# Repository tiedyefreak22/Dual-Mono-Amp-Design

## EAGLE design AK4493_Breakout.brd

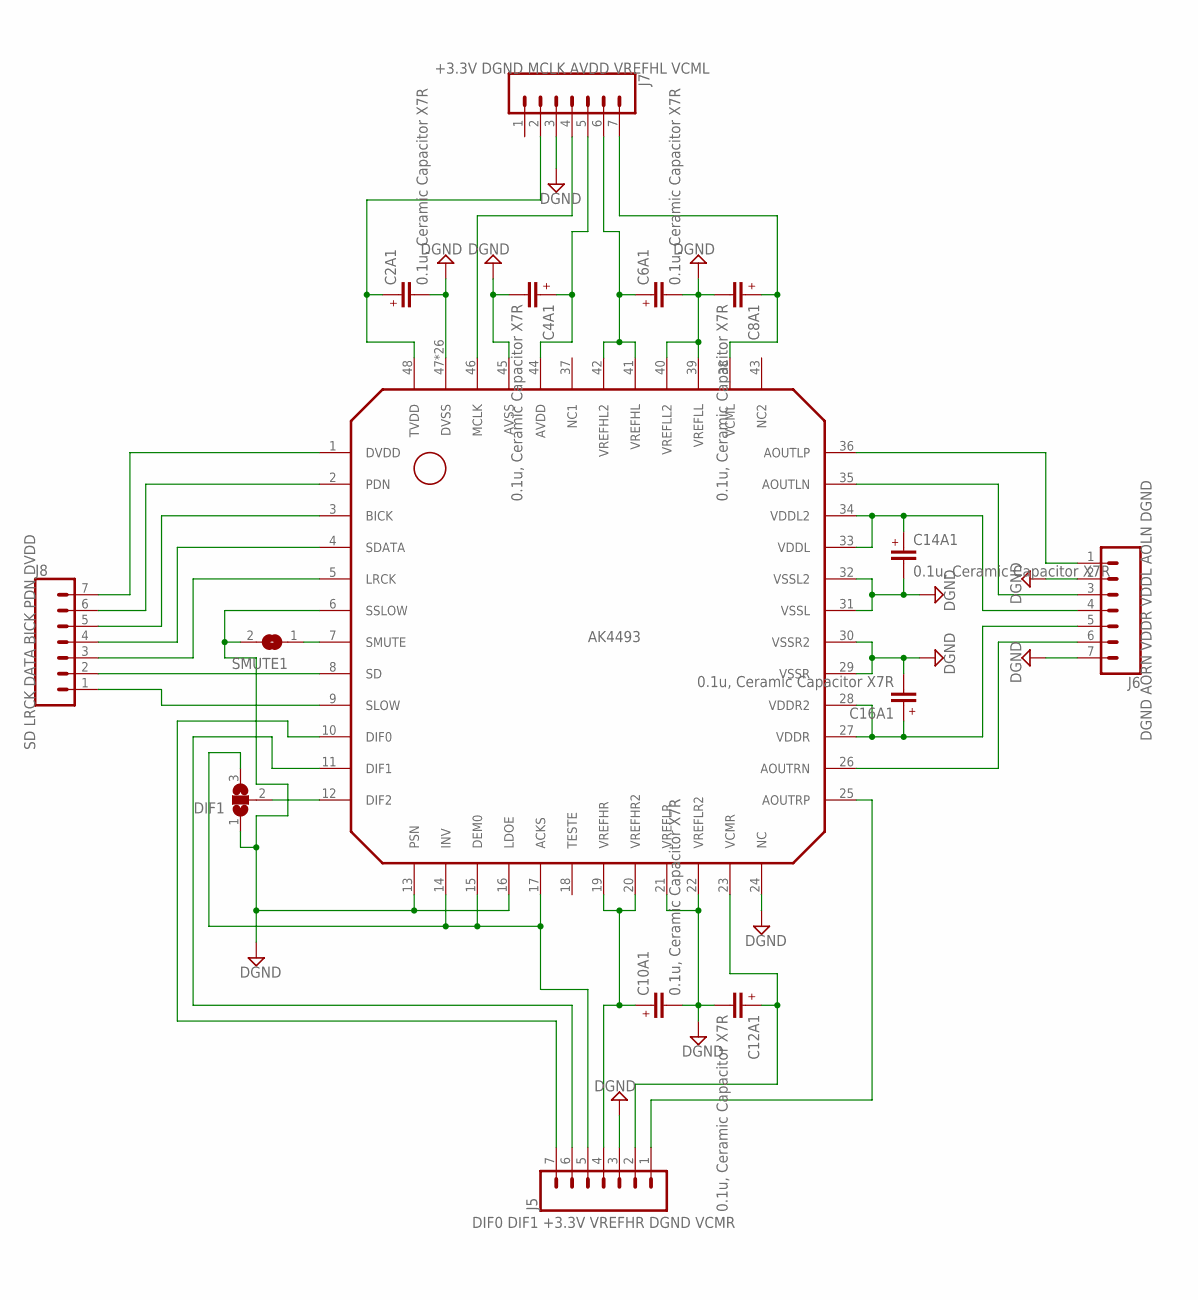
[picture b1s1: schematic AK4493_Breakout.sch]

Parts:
C2A1, C4A1, C6A1, C8A1, C10A1, C12A1, C14A1, C16A1: 0.1u, Ceramic Capacitor X7R; C0603K
DIF1: SJ2W; SJ_2
IC2: AK4493; LQFP48_
J5, J6, J7, J8: CONN_07; 1X07
SMUTE1: SJ

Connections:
DGND: C2A1.2, C2A1.DGND (2), C4A1.2, C4A1.DGND (2), C6A1.2, C6A1.DGND (2), C8A1.2, C8A1.DGND (2), C10A1.2, C10A1.DGND (2), C12A1.2, C12A1.DGND (2), C14A1.2, C14A1.DGND (2), C16A1.2, C16A1.DGND (2), DIF1.1, IC2.6 (SSLOW), IC2.13 (PSN), IC2.16 (LDOE), IC2.21 (VREFLR), IC2.22 (VREFLR2), IC2.24 (NC), IC2.29 (VSSR), IC2.30 (VSSR2), IC2.31 (VSSL), IC2.32 (VSSL2), IC2.39 (VREFLL), IC2.40 (VREFLL2), IC2.45 (AVSS), IC2.47 (DVSS), IC2.P$1 (DVSS), IC2.P$2 (DVSS), IC2.P$3 (DVSS), IC2.P$4 (DVSS), IC2.P$5 (DVSS), IC2.P$6 (DVSS), IC2.P$7 (DVSS), IC2.P$8 (DVSS), IC2.P$9 (DVSS), IC2.P$10 (DVSS), IC2.P$11 (DVSS), IC2.P$12 (DVSS), IC2.P$13 (DVSS), IC2.P$14 (DVSS), IC2.P$15 (DVSS), IC2.P$16 (DVSS), IC2.P$17 (DVSS), IC2.P$18 (DVSS), IC2.P$19 (DVSS), IC2.P$20 (DVSS), IC2.P$21 (DVSS), IC2.P$22 (DVSS), IC2.P$23 (DVSS), IC2.P$24 (DVSS), IC2.P$25 (DVSS), J5.3, J6.2, J6.7, J7.3, SMUTE1.2
unnamed: IC2.36 (AOUTLP), J6.1
unnamed: IC2.35 (AOUTLN), J6.3
unnamed: IC2.25 (AOUTRP), J5.1
unnamed: IC2.26 (AOUTRN), J6.6
unnamed: IC2.9 (SLOW), J8.1
unnamed: IC2.10 (DIF0), J5.7
unnamed: IC2.5 (LRCK), J8.3
unnamed: IC2.4 (SDATA), J8.4
unnamed: IC2.3 (BICK), J8.5
unnamed: IC2.46 (MCLK), J7.4
unnamed: IC2.1 (DVDD), J8.7
unnamed: C4A1.1, IC2.44 (AVDD), J7.5
unnamed: IC2.2 (PDN), J8.6
unnamed: C8A1.1, IC2.38 (VCML), J7.7
unnamed: C12A1.1, IC2.23 (VCMR), J5.2
unnamed: C6A1.1, IC2.41 (VREFHL), IC2.42 (VREFHL2), J7.6
unnamed: DIF1.2, IC2.12 (DIF2)
unnamed: IC2.7 (SMUTE), SMUTE1.1
unnamed: IC2.8 (SD), J8.2
unnamed: IC2.11 (DIF1), J5.6
unnamed: C10A1.1, IC2.19 (VREFHR), IC2.20 (VREFHR2), J5.4
unnamed: C14A1.1, IC2.33 (VDDL), IC2.34 (VDDL2), J6.4
unnamed: C16A1.1, IC2.27 (VDDR), IC2.28 (VDDR2), J6.5
unnamed: C2A1.1, IC2.48 (TVDD), J7.2
unnamed: DIF1.3, IC2.14 (INV), IC2.15 (DEM0), IC2.17 (ACKS), J5.5

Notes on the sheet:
+3.3V DGND MCLK AVDD VREFHL VCML
DIF0 DIF1 +3.3V VREFHR DGND VCMR
SD LRCK DATA BICK PDN DVDD
DGND AORN VDDR VDDL AOLN DGND

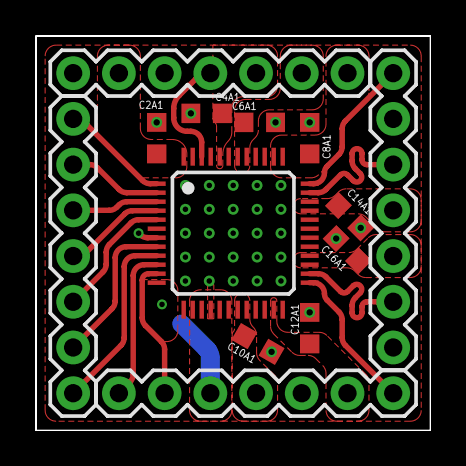
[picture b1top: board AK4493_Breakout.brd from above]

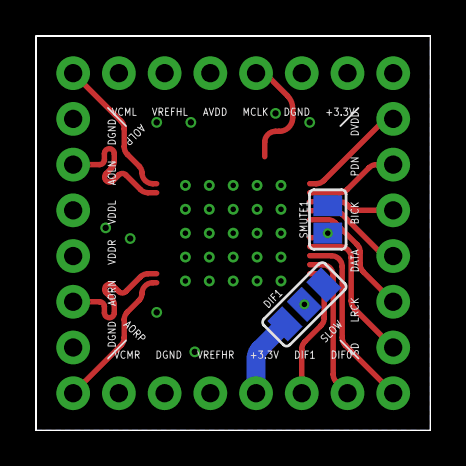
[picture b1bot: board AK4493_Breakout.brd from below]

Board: 2 copper layers, 21.9 x 21.9 mm, 15 parts (2 on the bottom side), 26 nets.

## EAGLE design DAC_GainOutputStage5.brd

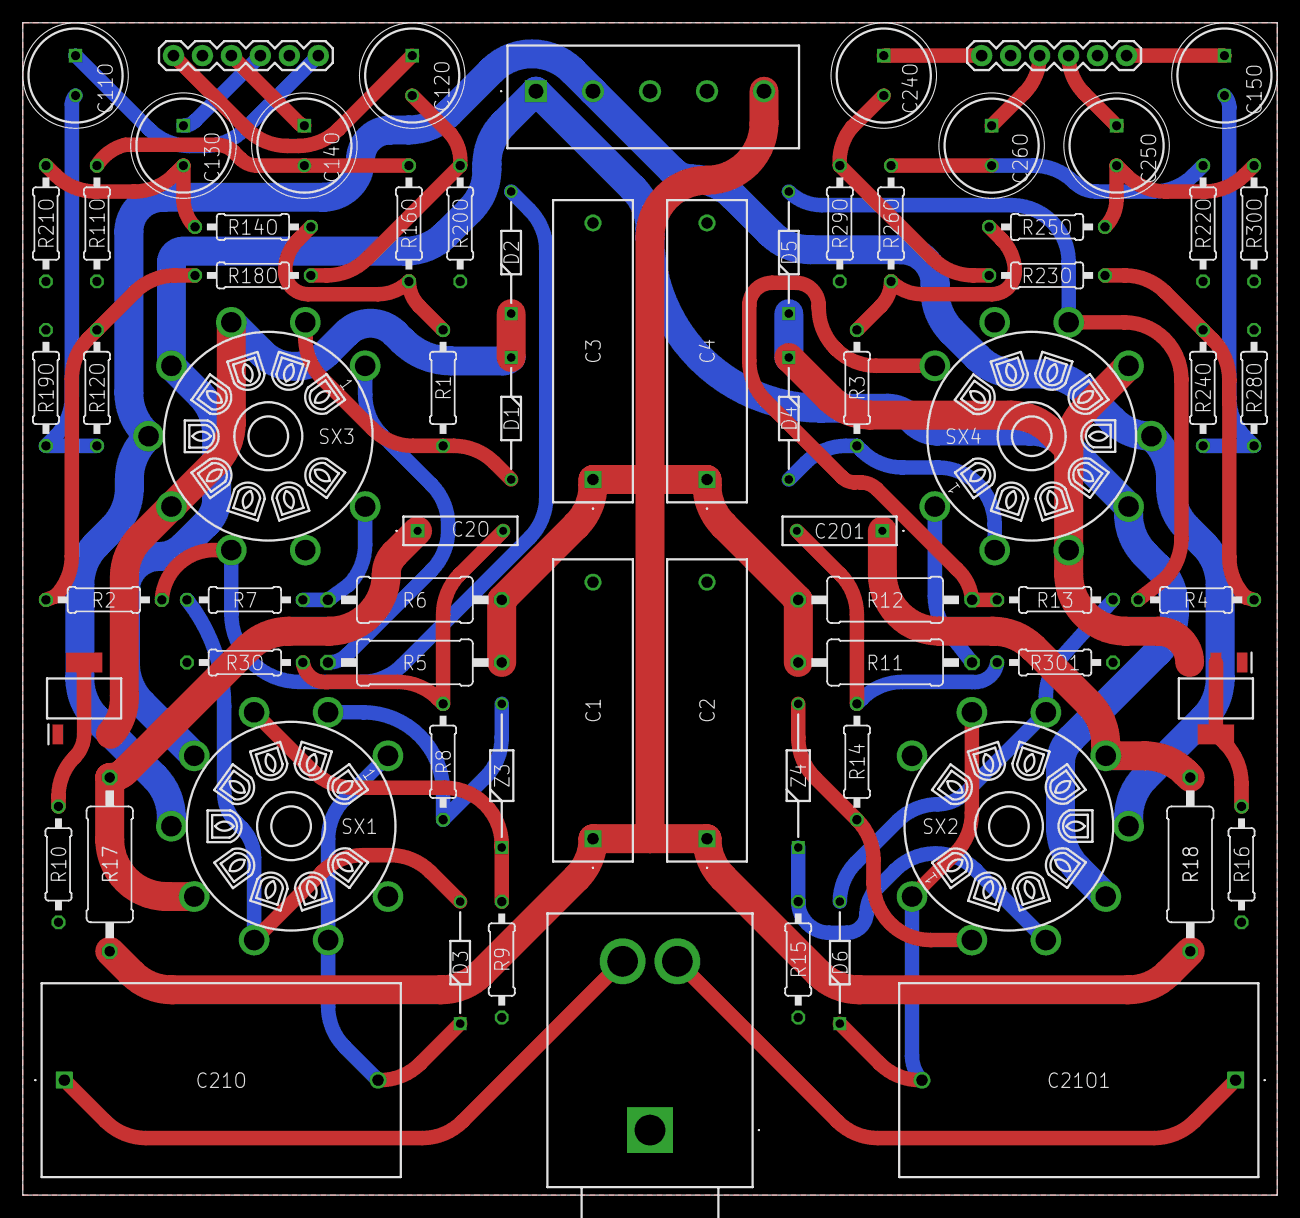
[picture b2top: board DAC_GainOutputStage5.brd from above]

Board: 2 copper layers, 110.0 x 102.8 mm, 70 parts (0 on the bottom side), 50 nets.

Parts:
C1, C2, C3, C4: MKP4G034705D00KSSD
C2O, C2O1: 0.1uF, 35V; MKS4B031002A00JC00
C11O, C12O, C13O, C14O, C15O, C24O, C25O, C26O: 100uF; CAPPRD350W60D825H1300
C21O, C21O1: 30uF/400V; DCP4G053006ID2KSSD
D1, D2, D3, D4, D5, D6: 1N4148-T50R; DIOAD1068W53L380D172
J1: 1935190
J2, J13: 1X06
J3: SJ-63033A; SJ63033A
R1, R2, R3, R4, R7, R8, R13, R14: 1k; 0207/10
R3O, R3O1: 1M*; 0207/10
R5, R6, R11, R12: 9.1k; 0411/15
R9, R15: 330; 0207/10
R10, R16: 48.7; 0207/10
R11O, R19O, R20O, R21O, R22O, R28O, R29O, R30O: 10k; 0207/10
R12O, R14O, R16O, R18O, R23O, R24O, R25O, R26O: 182; 0207/10
R17, R18: 499; 0411/15
SX1, SX2, SX3, SX4: VT9-PT
U1, U2: LM317MQDCYR; SOT230P700X180-4N
Z3, Z4: 1N750; DIOAD1256W56L444D203

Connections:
66.3VAC/1: J1.1, SX1.4, SX2.4, SX3.4, SX4.4
66.3VAC/2: J1.2, SX1.5, SX2.5, SX3.5, SX4.5
+240VDC: C1.1, C2.1, C3.1, C4.1, J1.5, R5.2, R6.2, R11.2, R12.2, R17.1, R18.2
AGND: C1.2, C2.2, C3.2, C4.2, J1.4, J2.2, J2.5, J3.1, J13.2, J13.5, R3O.2, R3O1.2, R9.1, R10.1, R11O.2, R15.1, R16.1, R19O.1, R20O.2, R21O.1, R22O.2, R28O.1, R29O.2, R30O.1, U1.1, U2.1
L+: R4.2, R23O.1, R24O.1
L-: R3.2, R25O.1, R26O.1
L_OUT: C21O1.1, J3.2
unnamed: R6.1, R7.2, SX3.9
unnamed: R8.1, SX1.2, Z3.2
unnamed: C21O1.2, D6.1, SX2.1, SX2.8
unnamed: D4.2, R3.1, SX4.2
unnamed: D5.2, R4.1, SX4.7
unnamed: D1.2, R1.1, SX3.2
unnamed: D4.1, D5.1, SX4.3, SX4.6, U2.3
unnamed: R11.1, SX4.1
unnamed: R12.1, R13.2, SX4.9
unnamed: C11O.1, J13.6
unnamed: C11O.2, R12O.2, R19O.2
unnamed: C15O.1, J2.6
unnamed: D2.2, R2.1, SX3.7
unnamed: R14.1, SX2.2, Z4.2
unnamed: C12O.1, J13.1
unnamed: C2O.2, R3O.1, R8.2
unnamed: C2O1.2, R3O1.1, R14.2
unnamed: C21O.2, D3.1, SX1.1, SX1.8
unnamed: C12O.2, R18O.2, R20O.1
unnamed: C15O.2, R24O.2, R28O.2
unnamed: C13O.1, J13.4
unnamed: D1.1, D2.1, SX3.3, SX3.6, U1.3
unnamed: D3.2, R7.1, SX1.7
unnamed: C14O.1, J13.3
unnamed: C14O.2, R11O.1, R16O.2
unnamed: R9.2, SX1.3, Z3.1
unnamed: R15.2, SX2.3, Z4.1
unnamed: C13O.2, R14O.2, R21O.2
unnamed: D6.2, R13.1, SX2.7
unnamed: C24O.1, J2.1
unnamed: C24O.2, R23O.2, R29O.1
unnamed: C25O.1, J2.4
unnamed: C26O.1, J2.3
unnamed: C26O.2, R22O.1, R26O.2
unnamed: R5.1, SX3.1
unnamed: C25O.2, R25O.2, R30O.2
unnamed: R10.2, U1.2, U1.4
unnamed: R16.2, U2.2, U2.4
unnamed: C2O.1, R17.2, SX1.6
unnamed: C2O1.1, R18.1, SX2.6
R+: R2.2, R12O.1, R18O.1
R-: R1.2, R14O.1, R16O.1
R_OUT: C21O.1, J3.3

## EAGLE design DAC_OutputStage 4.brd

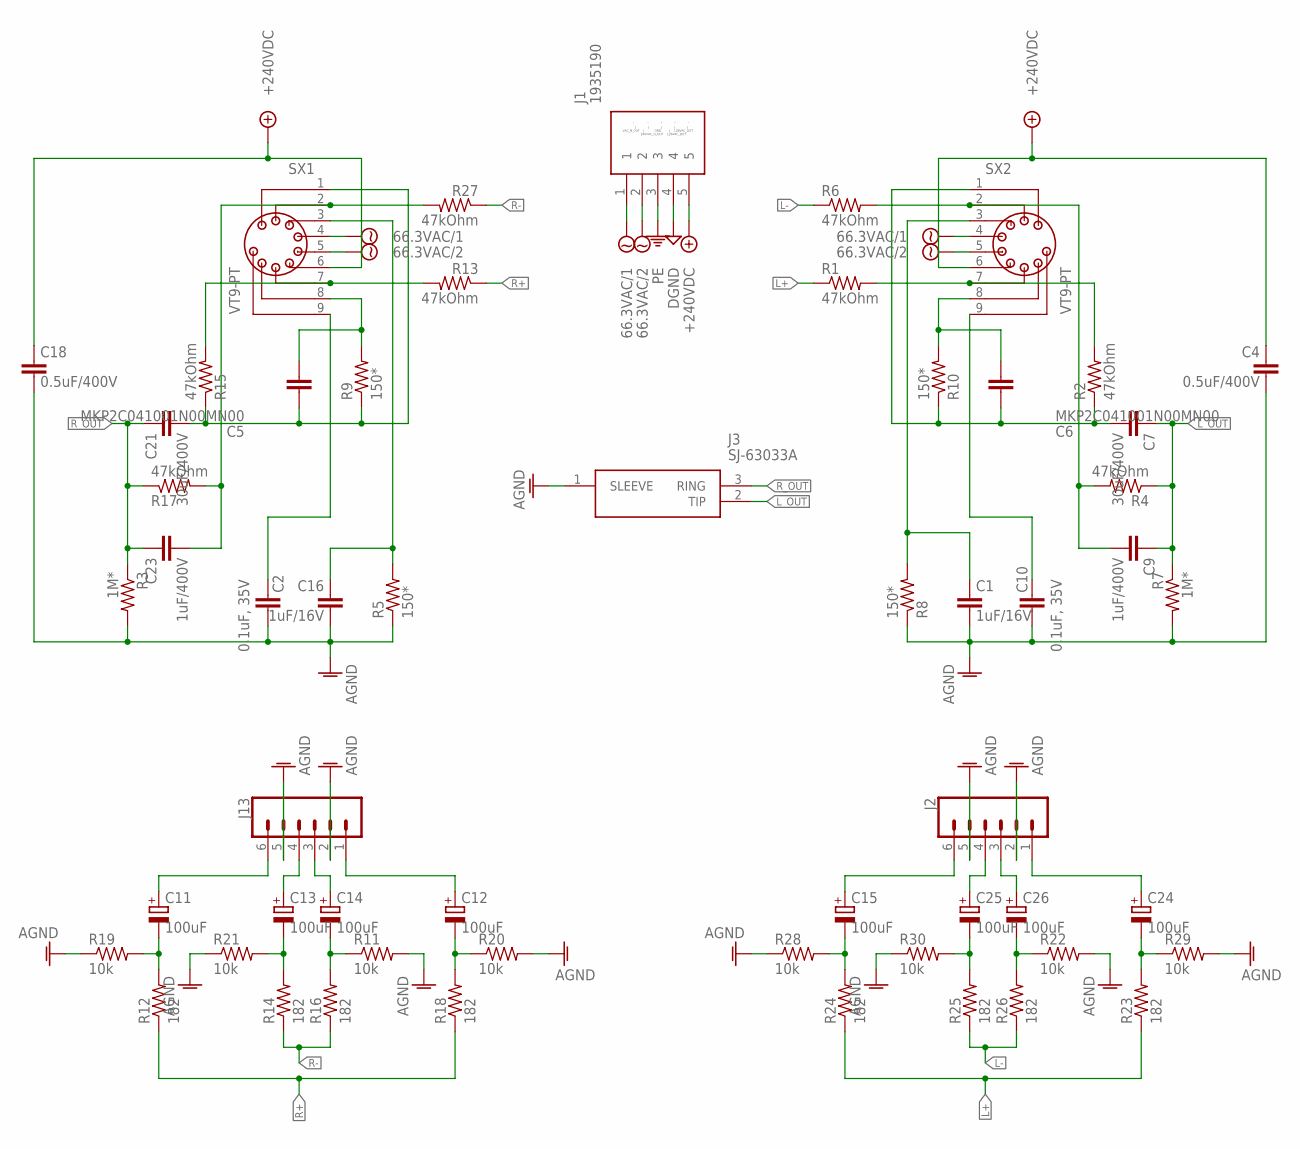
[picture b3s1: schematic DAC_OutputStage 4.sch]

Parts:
C1, C16: 1uF/16V; MKP2C041001N00MN00
C2, C10: 0.1uF, 35V; MKS4B031002A00JC00
C4, C18: 0.5uF/400V; MKP4G034705D00KSSD
C5, C6: MKP2C041001N00MN00
C7, C21: 30uF/400V; DCP4G053006ID2KSSD
C9, C23: 1uF/400V; MKP4G041005I00JSSD
C11, C12, C13, C14, C15, C24, C25, C26: 100uF; CAPPRD350W60D825H1300
J1: 1935190
J2, J13: CONN_06SILK_FEMALE_PTH; 1X06
J3: SJ-63033A; SJ63033A
R1, R2, R4, R6, R13, R15, R17, R27: 47kOhm; RESAD1540W55L620D230
R3, R7: 1M*; RESAD1540W60L620D230
R5, R8, R9, R10: 150*; RESAD1540W55L620D230
R11, R19, R20, R21, R22, R28, R29, R30: 10k; RESAD1540W55L620D230
R12, R14, R16, R18, R23, R24, R25, R26: 182; RESAD1590W60L630D240
SX1, SX2: VT9-PT

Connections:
66.3VAC/1: J1.1, SX1.4, SX2.4
66.3VAC/2: J1.2, SX1.5, SX2.5
+240VDC: C4.1, C18.1, J1.5, SX1.6, SX2.6
AGND: C1.2, C2.2, C4.2, C10.2, C16.2, C18.2, J2.2, J2.5, J3.1 (SLEEVE), J13.2, J13.5, R3.2, R5.1, R7.2, R8.1, R11.2, R19.1, R20.2, R21.1, R22.2, R28.1, R29.2, R30.1
DGND: J1.4
L+: R1.1, R23.1, R24.1
L-: R6.1, R25.1, R26.1
L_OUT: C7.1, C9.1, J3.2 (TIP), R4.1, R7.1
unnamed: C5.2, R9.2, SX1.8
unnamed: C2.1, SX1.9
unnamed: R1.2, R2.2, SX2.7
unnamed: C6.2, R10.2, SX2.8
unnamed: C6.1, C7.2, R2.1, R10.1, SX2.1
unnamed: C9.2, R4.2, R6.2, SX2.2
unnamed: C1.1, R8.2, SX2.3
unnamed: C10.1, SX2.9
unnamed: C11.1 (+), J13.6
unnamed: C11.2 (-), R12.2, R19.2
unnamed: C15.1 (+), J2.6
unnamed: C12.1 (+), J13.1
unnamed: R13.2, R15.2, SX1.7
unnamed: C5.1, C21.2, R9.1, R15.1, SX1.1
unnamed: C12.2 (-), R18.2, R20.1
unnamed: C15.2 (-), R24.2, R28.2
unnamed: C13.1 (+), J13.4
unnamed: C23.2, R17.2, R27.2, SX1.2
unnamed: C14.1 (+), J13.3
unnamed: C14.2 (-), R11.1, R16.2
unnamed: C16.1, R5.2, SX1.3
unnamed: C13.2 (-), R14.2, R21.2
unnamed: C24.1 (+), J2.1
unnamed: C24.2 (-), R23.2, R29.1
unnamed: C25.1 (+), J2.4
unnamed: C26.1 (+), J2.3
unnamed: C26.2 (-), R22.1, R26.2
unnamed: C25.2 (-), R25.2, R30.2
PE: J1.3
R+: R12.1, R13.1, R18.1
R-: R14.1, R16.1, R27.1
R_OUT: C21.1, C23.1, J3.3 (RING), R3.1, R17.1

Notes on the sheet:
^ ^ ^ ^ ^ | | | | | VAC_N_OUT | GND | 126VAC_OUT 240VAC_H_OUT 126VAC_OUT

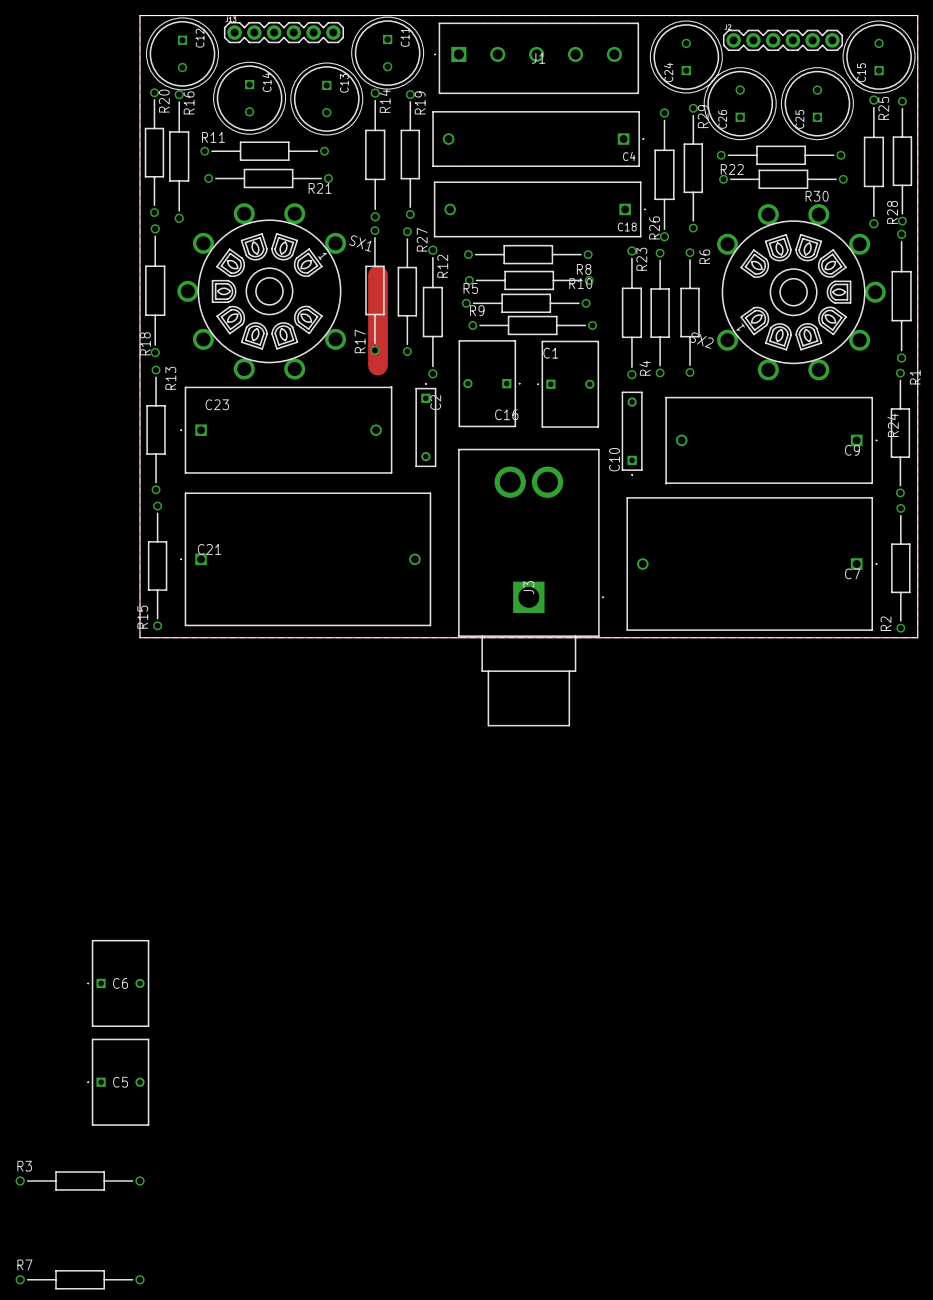
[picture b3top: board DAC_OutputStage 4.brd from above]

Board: 2 copper layers, 100.0 x 80.0 mm, 56 parts (0 on the bottom side), 38 nets.

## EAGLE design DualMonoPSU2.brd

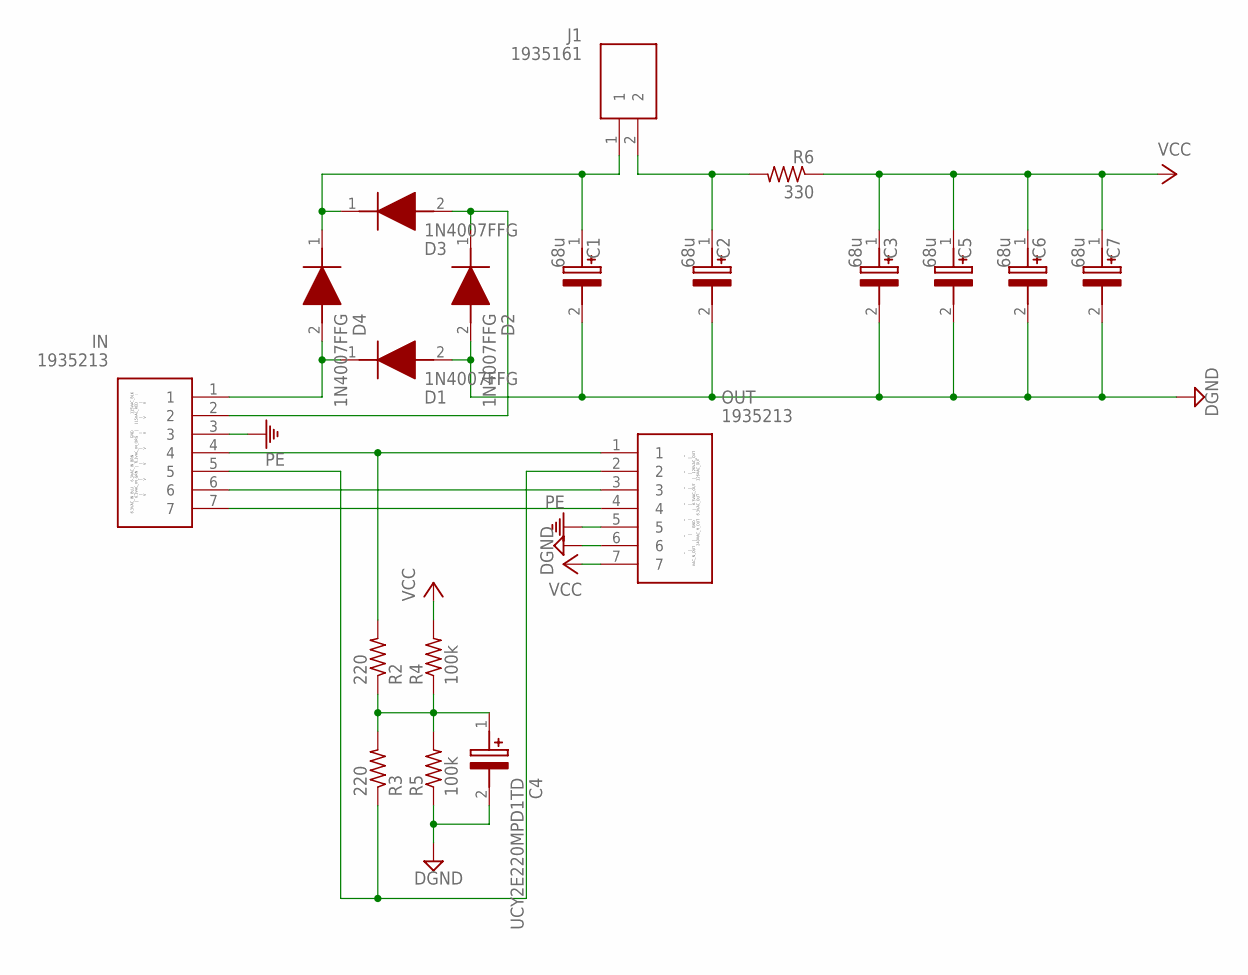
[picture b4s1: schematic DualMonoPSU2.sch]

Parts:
C1, C2, C3, C5, C6, C7: 68u; CAPPRD750W80D1475H4700
C4: UCY2E220MPD1TD; CAPPRD500W60D1025H1750
D1, D2, D3, D4: 1N4007FFG; DIOAD1405W86L465D235
IN: 1935213
J1: 1935161
OUT: 1935213
R2, R3: 220; 0411/15
R4, R5: 100k; 0411/15
R6: 330; 0411/15

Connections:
DGND: C1.2 (-), C2.2 (-), C3.2 (-), C4.2 (-), C5.2 (-), C6.2 (-), C7.2 (-), D1.2 (A), D2.2 (A), OUT.6, R5.1
unnamed: IN.5, OUT.2, R3.1
unnamed: D1.1 (K), D4.2 (A), IN.1
unnamed: C1.1 (+), D3.1 (K), D4.1 (K), J1.1
unnamed: D2.1 (K), D3.2 (A), IN.2
unnamed: C2.1 (+), J1.2, R6.2
unnamed: C4.1 (+), R2.1, R3.2, R4.1, R5.2
unnamed: IN.4, OUT.1, R2.2
unnamed: IN.6, OUT.3
unnamed: IN.7, OUT.4
PE: IN.3, OUT.5
VCC: C3.1 (+), C5.1 (+), C6.1 (+), C7.1 (+), OUT.7, R4.2, R6.1

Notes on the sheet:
6.3VAC_IN_BLU 6.3VAC_IN_BRN GND 115VAC_BLK | 6.3VAC_IN_GRN | 6.3VAC_IN_ORG | 115VAC_RED | | | | | | | | V V V V V V V
^ ^ ^ ^ ^ ^ ^ | | | | | | | VAC_N_OUT | GND | 6.3VAC_OUT | 126VAC_OUT 240VAC_H_OUT 6.3VAC_OUT 126VAC_OUT

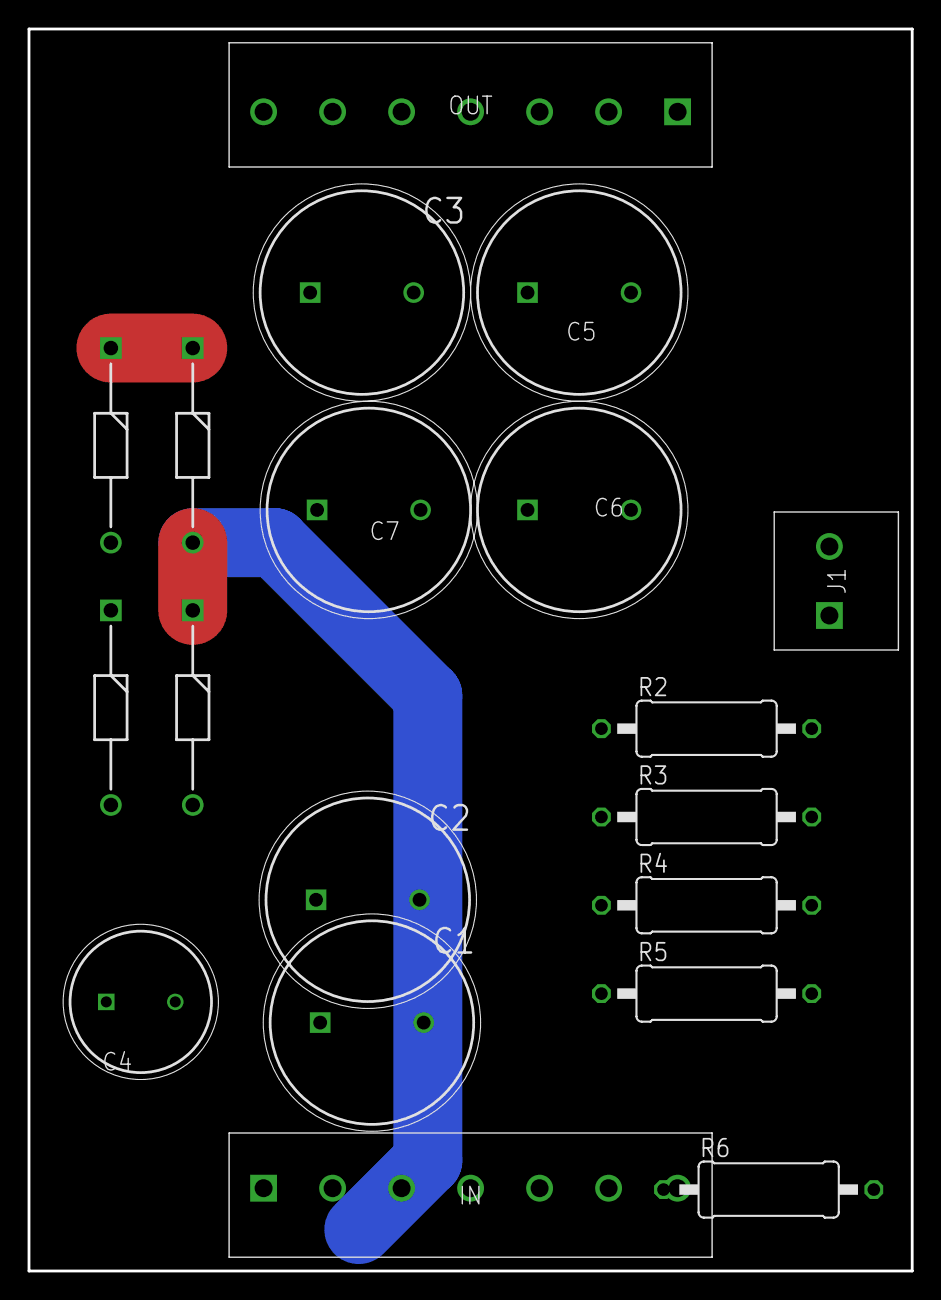
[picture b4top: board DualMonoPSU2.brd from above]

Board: 2 copper layers, 64.0 x 90.0 mm, 19 parts (0 on the bottom side), 12 nets.

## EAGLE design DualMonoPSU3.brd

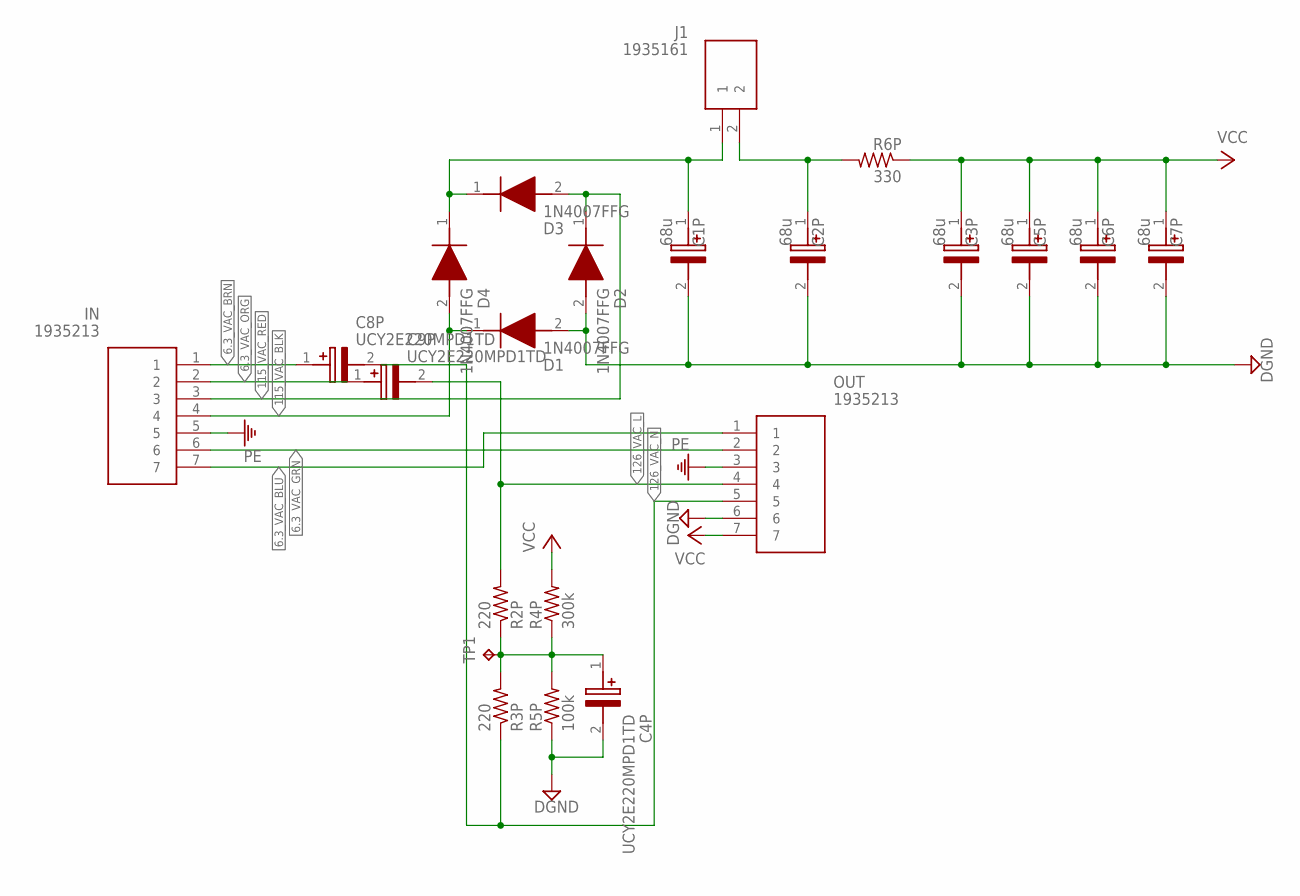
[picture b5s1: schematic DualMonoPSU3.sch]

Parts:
C1P, C2P, C3P, C5P, C6P, C7P: 68u; CAPPRD750W80D1475H4700
C4P, C8P, C9P: UCY2E220MPD1TD; CAPPRD500W60D1025H1750
D1, D2, D3, D4: 1N4007FFG; DIOAD1405W86L465D235
IN: 1935213
J1: 1935161
OUT: 1935213
R2P, R3P: 220; 0411/15
R4P: 300k; 0411/15
R5P: 100k; 0411/15
R6P: 330; 0411/15
TP1: TPB2,54; B2,54

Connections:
6.3_VAC_BLU: IN.7, OUT.1
6.3_VAC_BRN: C8P.1 (+), IN.1
6.3_VAC_GRN: IN.6, OUT.2
6.3_VAC_ORG: C9P.1 (+), IN.2
115_VAC_BLK: D1.1 (K), D4.2 (A), IN.4
115_VAC_RED: D2.1 (K), D3.2 (A), IN.3
126_VAC_L: C9P.2 (-), OUT.4, R2P.2
126_VAC_N: C8P.2 (-), OUT.5, R3P.1
DGND: C1P.2 (-), C2P.2 (-), C3P.2 (-), C4P.2 (-), C5P.2 (-), C6P.2 (-), C7P.2 (-), D1.2 (A), D2.2 (A), OUT.6, R5P.1
unnamed: C1P.1 (+), D3.1 (K), D4.1 (K), J1.1
unnamed: C2P.1 (+), J1.2, R6P.2
unnamed: C4P.1 (+), R2P.1, R3P.2, R4P.1, R5P.2, TP1.TP
PE: IN.5, OUT.3
VCC: C3P.1 (+), C5P.1 (+), C6P.1 (+), C7P.1 (+), OUT.7, R4P.2, R6P.1

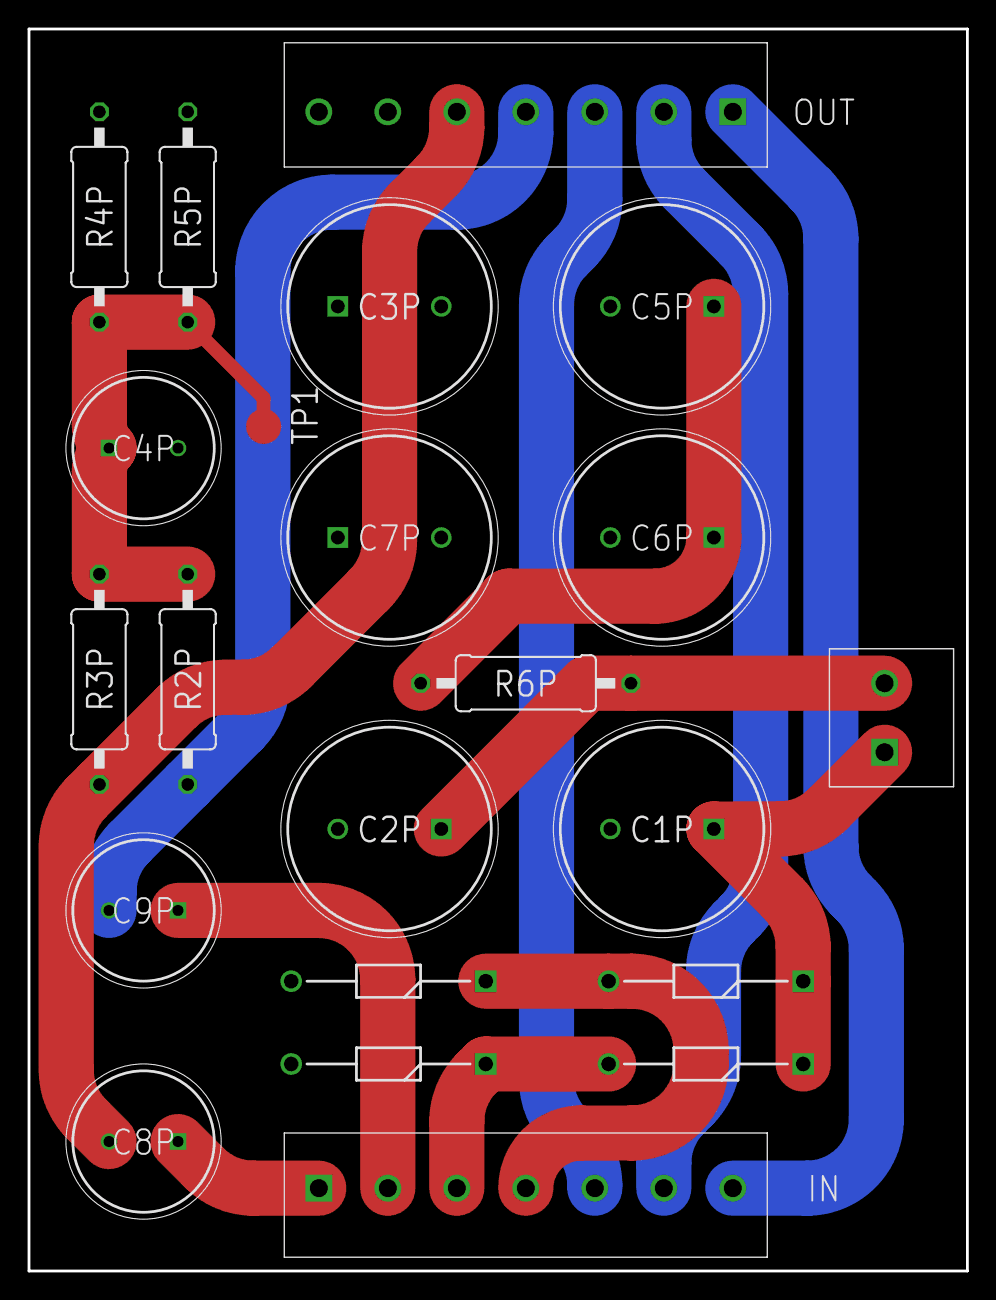
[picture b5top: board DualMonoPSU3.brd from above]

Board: 2 copper layers, 68.0 x 90.0 mm, 22 parts (0 on the bottom side), 14 nets.

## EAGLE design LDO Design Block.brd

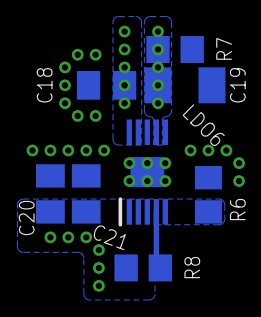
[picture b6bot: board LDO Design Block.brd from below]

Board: 2 copper layers, 8 parts (8 on the bottom side), 6 nets.

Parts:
C18, C20, C21: C0805K
C19: C1206K
LDO6: LT3042; SOP50P490X110-11N
R6, R7, R8: R0805

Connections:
DGND: C18.1, C19.1, C20.1, C21.1, LDO6.8, LDO6.11, R6.2, R7.2
unnamed: LDO6.5, R6.1
unnamed: C19.2, LDO6.7, R7.1
unnamed: LDO6.4, R8.2
unnamed: C20.2, C21.2, LDO6.1, LDO6.2, LDO6.3, R8.1
unnamed: C18.2, LDO6.9, LDO6.10
